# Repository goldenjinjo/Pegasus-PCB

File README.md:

Schematic And PCB Design for Pegasus Flight Computer in Kicad. 
Designed to track 3D position via GPS and transmit to ground station.
Originally developed for the UNSW Rocketry Team.

**PARTS LIST:**

- Microprocessor: Teensy 4
- GPS: Quectel L70B-M39
- Radio Transceiver: RFD900ux
- Memory: XTSD 4GB NAND Flash
- RGB LED

---
## 📸 Overview

### 📐 PCB Layout

**Dimensions**: 
- 98.0 mm × 39 mm board length
- 98.0mm x 57.74 mm maximum horizontal (due to antennas)
  
**Mounting Holes**: ⌀3.2 mm (4-cornered)

---
## 📊 Schematic

---

### ⚙️ Render – Front Side

---

### 🔧 Render – Back Side

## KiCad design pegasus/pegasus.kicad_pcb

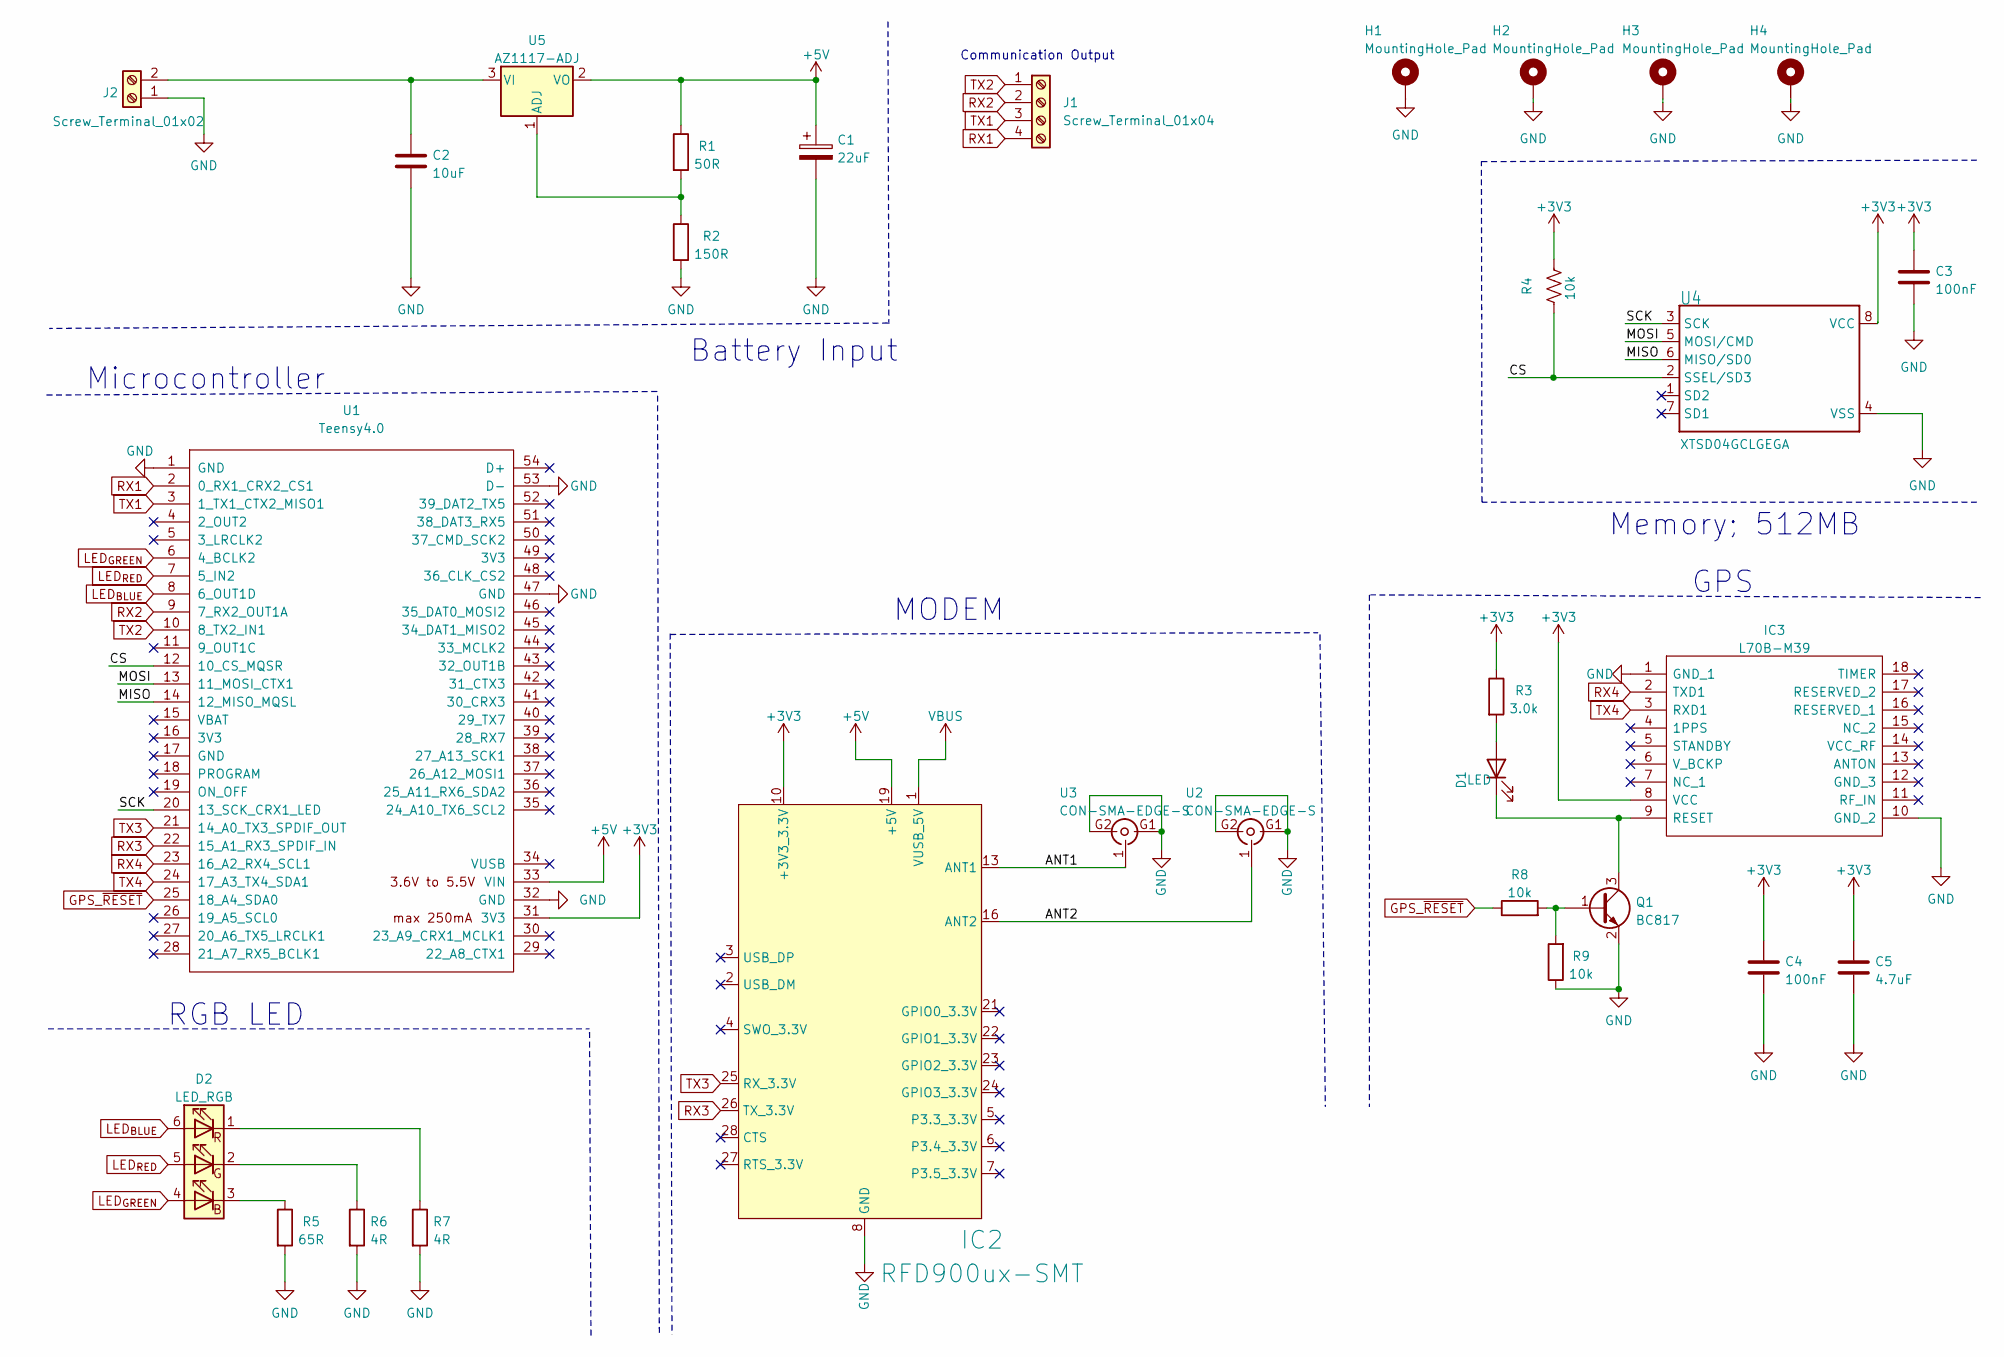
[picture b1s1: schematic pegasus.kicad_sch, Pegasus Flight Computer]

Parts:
C1: 22uF; CP_EIA-7343-30_AVX-N
C2: 10uF; C_0805_2012Metric
C3, C4: 100nF; C_0805_2012Metric
C5: 4.7uF; C_1206_3216Metric
D1: LED; LED_miniPLCC_2315
D2: LED_RGB; LED_RGB_5050-6
H1, H2, H3, H4: MountingHole_Pad; MountingHole_3.2mm_M3_Pad
IC2: RFD900ux-SMT; 1x28
IC3: L70B-M39; 1x18; Manufacturer_Part_Number L70B-M39; Mouser Part Number 277-L70B-M39
J1: Screw_Terminal_01x04; SHDR4W100P0X500_1X4_2000X800X1000P
J2: Screw_Terminal_01x02; SHDR2W105P0X500_1X2_1060X900X1250P
Q1: BC817; SOT-23
R1: 50R; C_0402_1005Metric
R2: 150R; C_0402_1005Metric
R3: 3.0k; R_0603_1608Metric
R4: 10k; R_0603_1608Metric; LCSC C332266
R5: 65R; R_0603_1608Metric
R6, R7: 4R; R_0603_1608Metric
R8, R9: 10k; R_0603_1608Metric
U1: Teensy4.0; Teensy40
U2, U3: CON-SMA-EDGE-S; RFSOLUTIONS_CON-SMA-EDGE-S
U4: XTSD04GCLGEGA; LGA8_8X6; LCSC C2759953
U5: AZ1117-ADJ; SOT-223-3_TabPin2

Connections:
+3V3: C3.1, C4.1, C5.1, IC2.10 (+3V3_3.3V), IC3.8 (VCC), R3.1, R4.1, U1.31 (3V3), U4.8 (VCC)
+5V: C1.1, IC2.19 (+5V), R1.1, U1.33 (VIN), U5.2 (VO)
/ANT1: IC2.13 (ANT1), U3.1
/ANT2: IC2.16 (ANT2), U2.1
/CS: R4.2, U1.12 (10_CS_MQSR), U4.2 (SSEL/SD3)
/MISO: U1.14 (12_MISO_MQSL), U4.6 (MISO/SD0)
/MOSI: U1.13 (11_MOSI_CTX1), U4.5 (MOSI/CMD)
/SCK: U1.20 (13_SCK_CRX1_LED), U4.3 (SCK)
GND: C1.2, C2.2, C3.2, C4.2, C5.2, H1.1, H2.1, H3.1, H4.1, IC2.8 (GND), IC2.9 (GND), IC2.11 (GND), IC2.12 (GND), IC2.14 (GND), IC2.15 (GND), IC2.17 (GND), IC2.18 (GND), IC2.20 (GND), IC3.1 (GND_1), IC3.10 (GND_2), J2.1, Q1.2 (E), R2.2, R5.2, R6.2, R7.2, R9.1, U1.1 (GND), U1.32 (GND), U1.47 (GND), U1.53 (D-), U2.G1, U2.G2, U3.G1, U3.G2, U4.4 (VSS)
GPS_~RESET: R8.1, U1.25 (18_A4_SDA0)
LED_{BLUE}: D2.4 (BA), U1.6 (4_BCLK2)
LED_{GREEN: D2.5 (GA), U1.7 (5_IN2)
LED_{RED}: D2.6 (RA), U1.8 (6_OUT1D)
unnamed: C2.1, J2.2, U5.3 (VI)
unnamed: D1.1 (K), IC3.9 (RESET), Q1.3 (C)
unnamed: D1.2 (A), R3.2
unnamed: D2.1 (RK), R7.1
unnamed: D2.2 (GK), R6.1
unnamed: D2.3 (BK), R5.1
unnamed: Q1.1 (B), R8.2, R9.2
unnamed: R1.2, R2.1, U5.1 (ADJ)
RX1: J1.4, U1.2 (0_RX1_CRX2_CS1)
RX2: J1.2, U1.9 (7_RX2_OUT1A)
RX3: IC2.26 (TX_3.3V), U1.22 (15_A1_RX3_SPDIF_IN)
RX4: IC3.2 (TXD1), U1.23 (16_A2_RX4_SCL1)
TX1: J1.3, U1.3 (1_TX1_CTX2_MISO1)
TX2: J1.1, U1.10 (8_TX2_IN1)
TX3: IC2.25 (RX_3.3V), U1.21 (14_A0_TX3_SPDIF_OUT)
TX4: IC3.3 (RXD1), U1.24 (17_A3_TX4_SDA1)
VBUS: IC2.1 (VUSB_5V)

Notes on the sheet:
Battery Input
Communication Output
GPS
Memory; 512MB
Microcontroller
MODEM
RGB LED

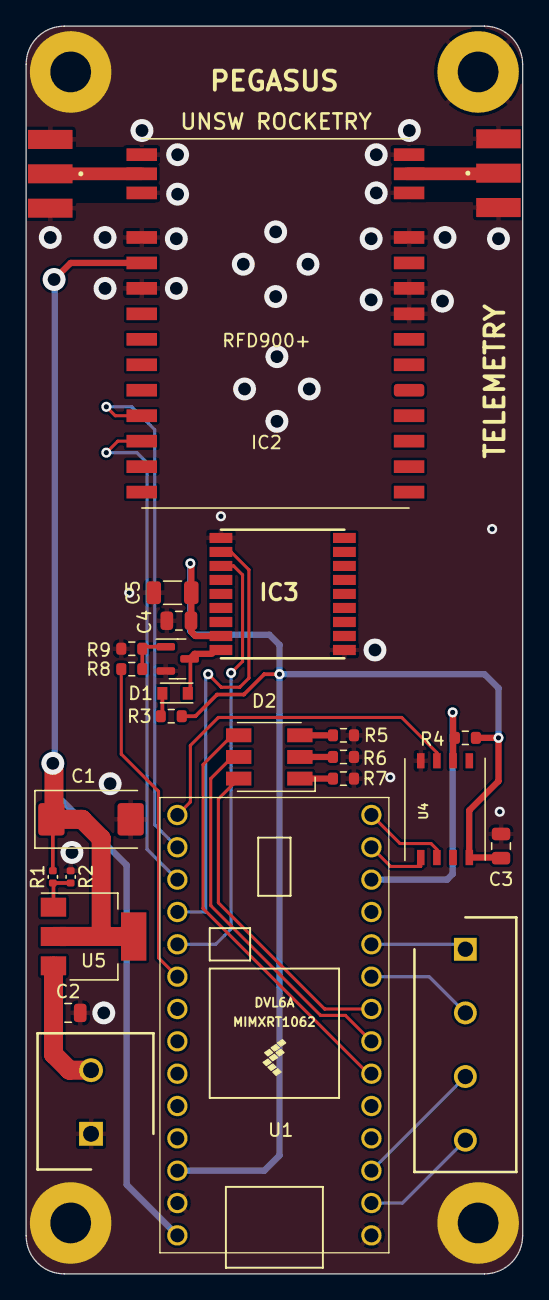
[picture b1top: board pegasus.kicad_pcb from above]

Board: 2 copper layers, 39.0 x 98.0 mm, 30 parts (0 on the bottom side), 29 nets.

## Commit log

2022-06-28 import pegasus project file from hardware repo, add readme and .gitignore
2022-06-28 Update README.md
    remove bellerophon parts list
2022-06-30 replace teensy 4.1 wih teensy 4, remove barometer and IMU
2022-06-30 replace sma-connectors with screw terminal with switch
2022-06-30 add external RX TX connectors
2022-06-30 add rgb led
2022-07-21 change mount holes to m3, draft new component layout, reduce size to 39x105mm
2022-07-21 add second rx-tx screw terminal connector, optimize pin assignment for other components
2022-07-21 add xtsd footprint library, and xtsd nand chip to pcb
2022-07-21 re add ground plane
2022-07-26 add borders and titles to components in schematic
2022-07-26 add datasheets
2022-07-27 add some traces
2022-07-27 New voltage regulator added to schematic and pcb
2022-07-28 add vias to top through holes, change antenna to route to common ground
2022-07-28 Route LED and memory on PCB
2022-08-10 Voltage regulator fixes
2022-08-10 increasing spacing of components, route rx-tx of gps
2022-08-10 route GND and 3.3V traces
2022-08-10 move rfd900 closer to gps, decrease length to 98mm
2022-08-11 route all traces to rfd900
2022-08-11 add via stitching and more spacing between traces
2022-08-11 add missing round pin to rfd900
2022-08-11 remove unused teensy 4 pins from footprint
2022-09-23 replace voltage regulator with 1A capable, variable regulator. Increase via size for PCB mill prototyping. Add more vias for RFD900
2022-09-23 add headings to and general clean up to schematic
2022-09-23 reposition GPS to center of board, add gps reset circuitry
2022-10-01 change LED pin names to reflect proper colors
2023-10-16 clean silkscreen
2025-04-24 move logo into component libraries
2025-04-24 remove depreacted libraries
2025-04-24 remove unneccessary GPS footprint info, clean up fabs
2025-04-24 add dimensions to PCB
2025-04-24 add design images
2025-04-24 remove deprecated datasheets
